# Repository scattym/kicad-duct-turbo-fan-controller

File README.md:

# kicad-duct-turbo-fan-controller
Wifi enabled fan controller projects for the duct turbo (ducturbo), terrabloom and ac infinity fans

Simple project marrying up 3 premade boards, the esp32 doit v2, a buck-boost board and a scd41 board.

Connects to the ducturbo 3.5mm to PWM control the fan speed.

Low side mosfet PWM chosen so that removal (or potentially failure) of the esp32 keeps the fan off.

Board will also work with the AC Infinity fans however there seems to be in internal 10k resistor on these fans, so changing R5 from 10K to 1K is needed to get the "off" voltage down to under 1 volt. With the following pins:

GND → GND

10V → VBUS

PWM → D+

TACH → D-

duct-turbo-fan-controller - original based of esp32 doit it board - done - tested

duct-turbo-fan-controller-v2 - moved to esp32-c3-wroom-02 - done - waiting testing

duct-turbo-fan-controller-v3 - add bme680 on board allow usb to power esp for programming - done - untested

duct-turbo-fan-controller-v4 - on board buck converter and on board scd41 - done - waiting testing

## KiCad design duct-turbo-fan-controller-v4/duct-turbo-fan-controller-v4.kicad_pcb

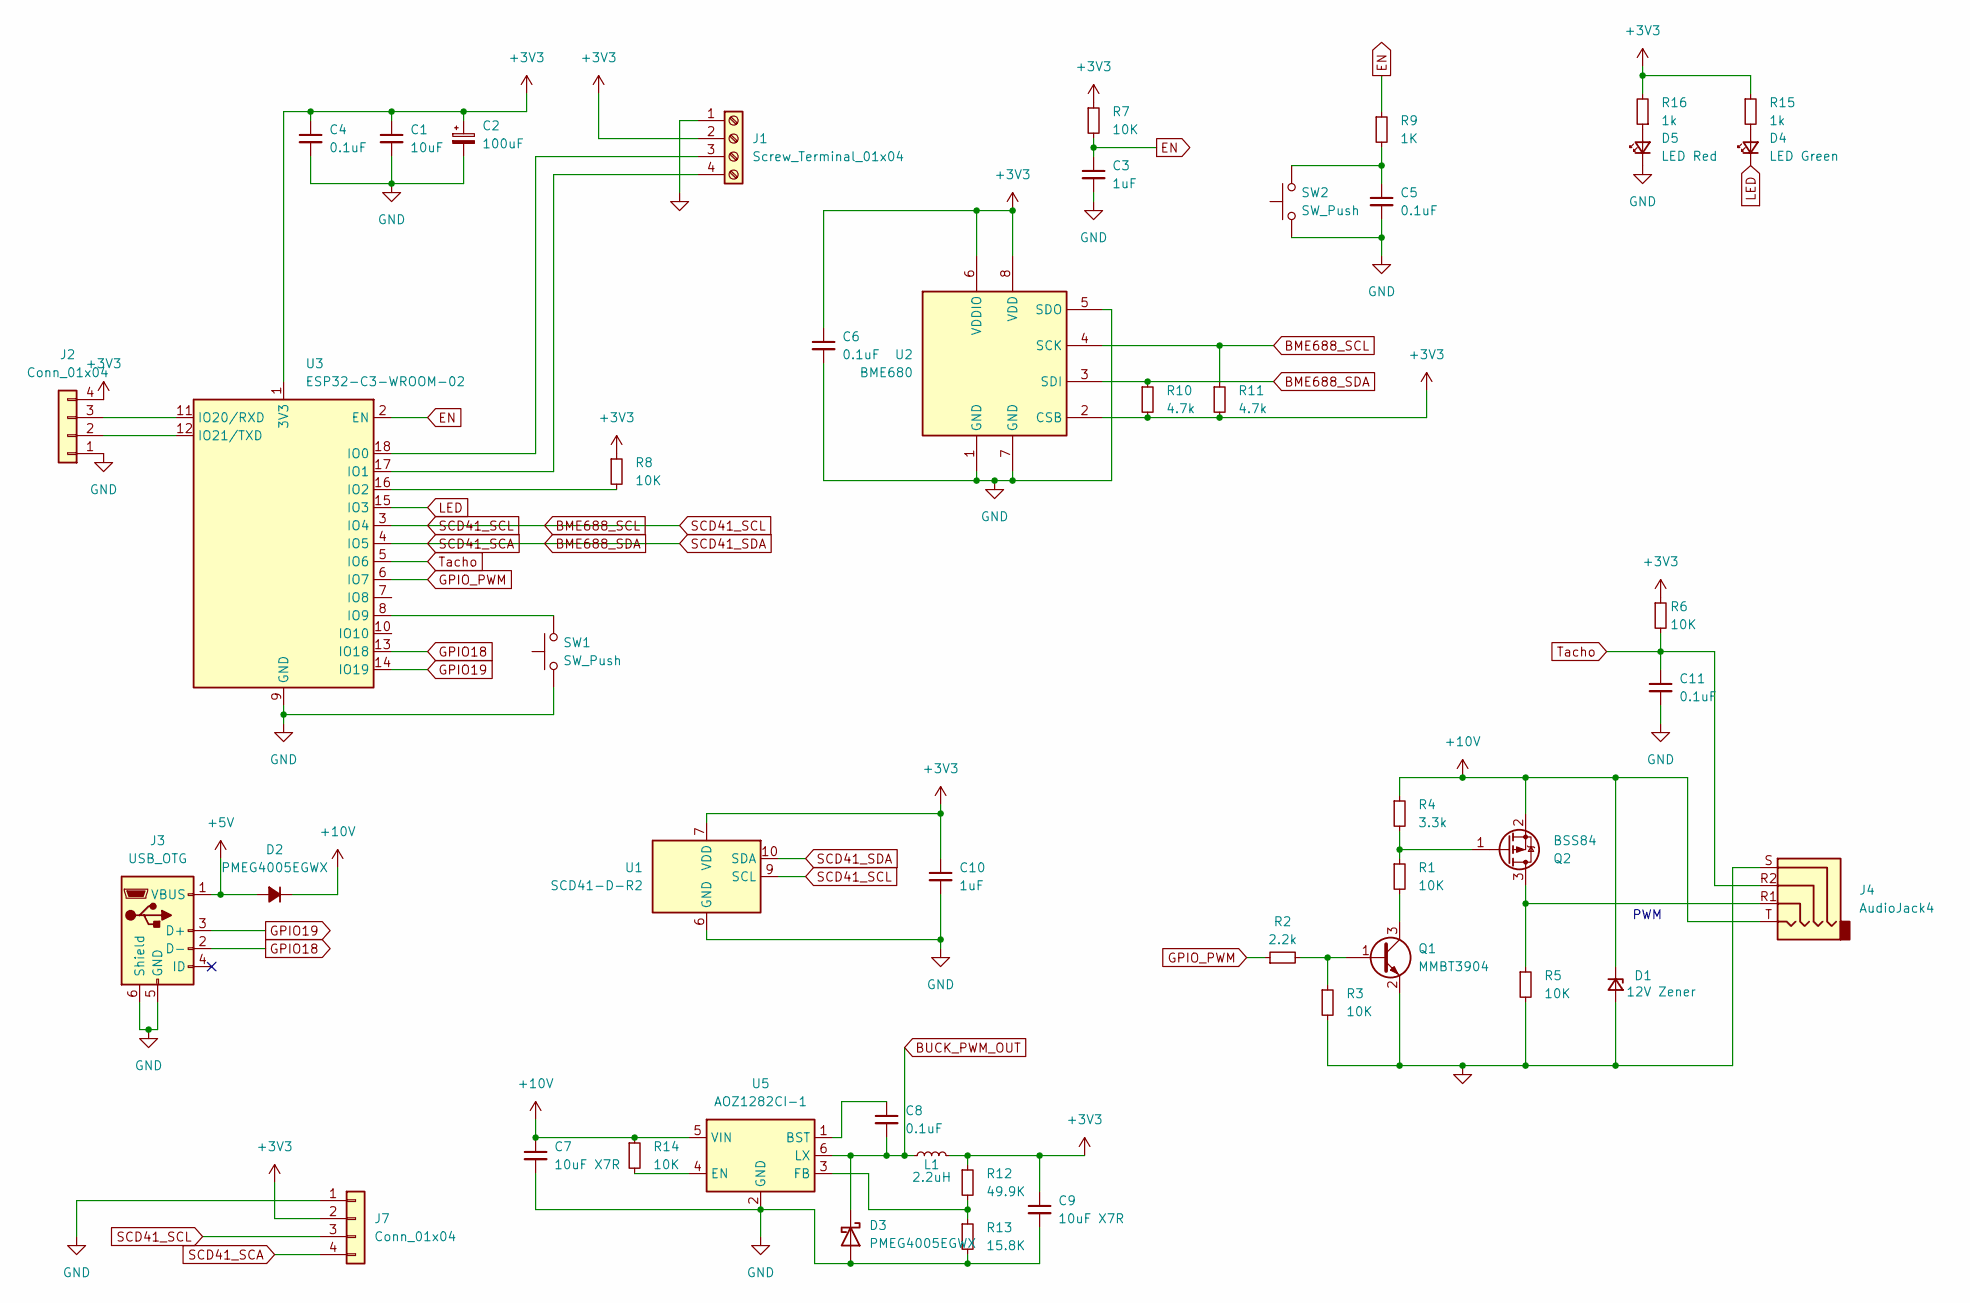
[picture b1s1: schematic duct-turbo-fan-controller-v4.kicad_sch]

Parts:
C1: 10uF; C_0805_2012Metric_Pad1.18x1.45mm_HandSolder
C2: 100uF; CP_EIA-3528-12_Kemet-T_Pad1.50x2.35mm_HandSolder
C3, C10: 1uF; C_0805_2012Metric_Pad1.18x1.45mm_HandSolder
C4, C5, C8: 0.1uF; C_0805_2012Metric_Pad1.18x1.45mm_HandSolder
C6, C11: 0.1uF; C_0603_1608Metric_Pad1.08x0.95mm_HandSolder
C7, C9: 10uF X7R; C_0805_2012Metric_Pad1.18x1.45mm_HandSolder
D1: 12V Zener; D_0805_2012Metric_Pad1.15x1.40mm_HandSolder
D2, D3: PMEG4005EGWX; D_SOD-123
D4: LED Green; LED_0603_1608Metric_Pad1.05x0.95mm_HandSolder
D5: LED Red; LED_0603_1608Metric_Pad1.05x0.95mm_HandSolder
J1: Screw_Terminal_01x04; TerminalBlock_Phoenix_MPT-0,5-4-2.54_1x04_P2.54mm_Horizontal
J2, J7: Conn_01x04; PinHeader_1x04_P2.54mm_Vertical
J3: USB_OTG; USB_Micro-B_Molex-105017-0001
J4: AudioJack4; Jack_3.5mm_KoreanHropartsElec_PJ-320D-4A_Horizontal
L1: 2.2uH; L_Bourns-SRN4018
Q1: MMBT3904; SOT-23
Q2: BSS84; SOT-23
R1, R3, R5, R7, R14: 10K; R_0805_2012Metric_Pad1.20x1.40mm_HandSolder
R2: 2.2k; R_0805_2012Metric_Pad1.20x1.40mm_HandSolder
R4: 3.3k; R_0805_2012Metric_Pad1.20x1.40mm_HandSolder
R6, R8: 10K; R_0603_1608Metric_Pad0.98x0.95mm_HandSolder
R9: 1K; R_0805_2012Metric_Pad1.20x1.40mm_HandSolder
R10, R11: 4.7k; R_0603_1608Metric_Pad0.98x0.95mm_HandSolder
R12: 49.9K; R_0805_2012Metric_Pad1.20x1.40mm_HandSolder
R13: 15.8K; R_0805_2012Metric_Pad1.20x1.40mm_HandSolder
R15, R16: 1k; R_0603_1608Metric_Pad0.98x0.95mm_HandSolder
SW1, SW2: SW_Push; SW_SPST_CK_RS282G05A3
U1: SCD41-D-R2; Sensirion_SCD4x-1EP_10.1x10.1mm_P1.25mm_EP4.8x4.8mm
U2: BME680; Bosch_LGA-8_3x3mm_P0.8mm_ClockwisePinNumbering
U3: ESP32-C3-WROOM-02
U5: AOZ1282CI-1; SOT-23-6

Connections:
+3V3: C1.1, C2.1, C4.1, C6.1, C9.1, C10.1, J1.2, J2.4, J7.2, L1.2, R6.1, R7.1, R8.1, R10.2, R11.2, R12.1, R15.1, R16.2, U1.7 (VDD), U1.19 (VDD), U2.2 (CSB), U2.6 (VDDIO), U2.8 (VDD), U3.1 (3V3)
+5V: D2.2 (A), J3.1 (VBUS)
+10V: C7.1, D1.1 (K), D2.1 (K), J4.T, Q2.2 (S), R4.1, R14.1, U5.5 (VIN)
BME688_SCL: J7.3, R11.1, U1.9 (SCL), U2.4 (SCK), U3.3 (IO4)
BME688_SDA: J7.4, R10.1, U1.10 (SDA), U2.3 (SDI), U3.4 (IO5)
BUCK_PWM_OUT: C8.2, D3.1 (K), L1.1, U5.6 (LX)
EN: C3.1, R7.2, R9.1, U3.2 (EN)
GND: C1.2, C2.2, C3.2, C4.2, C5.2, C6.2, C7.2, C9.2, C10.2, C11.2, D1.2 (A), D3.2 (A), D5.1 (K), J1.1, J2.1, J3.5 (GND), J3.6 (Shield), J4.S, J7.1, Q1.2 (E), R3.2, R5.2, R13.2, SW1.1, SW2.1, U1.6 (GND), U1.20 (GND), U1.21 (GND), U2.1 (GND), U2.5 (SDO), U2.7 (GND), U3.9 (GND), U3.19 (GND), U5.2 (GND)
GPIO18: J3.2 (D-), U3.13 (IO18)
GPIO19: J3.3 (D+), U3.14 (IO19)
GPIO_PWM: R2.1, U3.6 (IO7)
LED: D4.1 (K), U3.15 (IO3)
unnamed: C5.1, R9.2, SW2.2
unnamed: D4.2 (A), R15.2
unnamed: D5.2 (A), R16.1
unnamed: J1.3, U3.18 (IO0)
unnamed: J1.4, U3.17 (IO1)
unnamed: J2.2, U3.12 (IO21/TXD)
unnamed: J2.3, U3.11 (IO20/RXD)
unnamed: Q1.1 (B), R2.2, R3.1
unnamed: Q1.3 (C), R1.2
unnamed: J4.R1, Q2.3 (D), R5.1
unnamed: Q2.1 (G), R1.1, R4.2
unnamed: R8.2, U3.16 (IO2)
unnamed: SW1.2, U3.8 (IO9)
unnamed: C8.1, U5.1 (BST)
unnamed: R14.2, U5.4 (EN)
unnamed: R12.2, R13.1, U5.3 (FB)
Tacho: C11.1, J4.R2, R6.2, U3.5 (IO6)

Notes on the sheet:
PWM

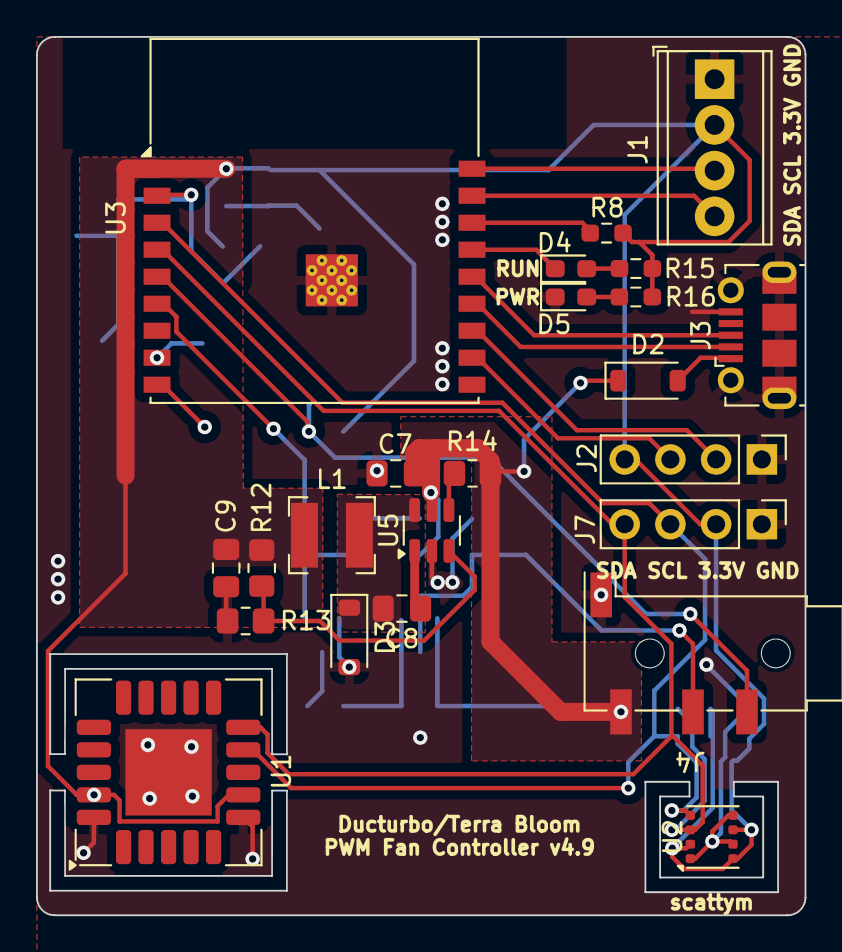
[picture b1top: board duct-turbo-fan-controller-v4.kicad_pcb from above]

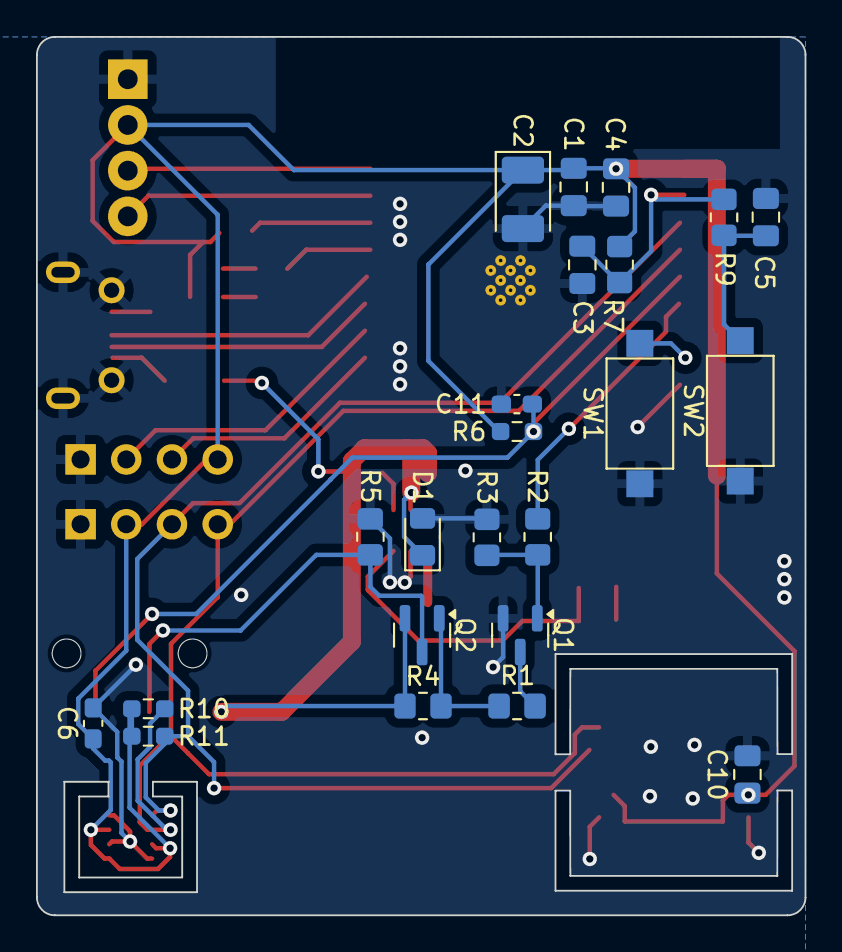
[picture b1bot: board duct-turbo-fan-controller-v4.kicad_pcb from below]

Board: 2 copper layers, 42.7 x 48.8 mm, 46 parts (23 on the bottom side), 29 nets.

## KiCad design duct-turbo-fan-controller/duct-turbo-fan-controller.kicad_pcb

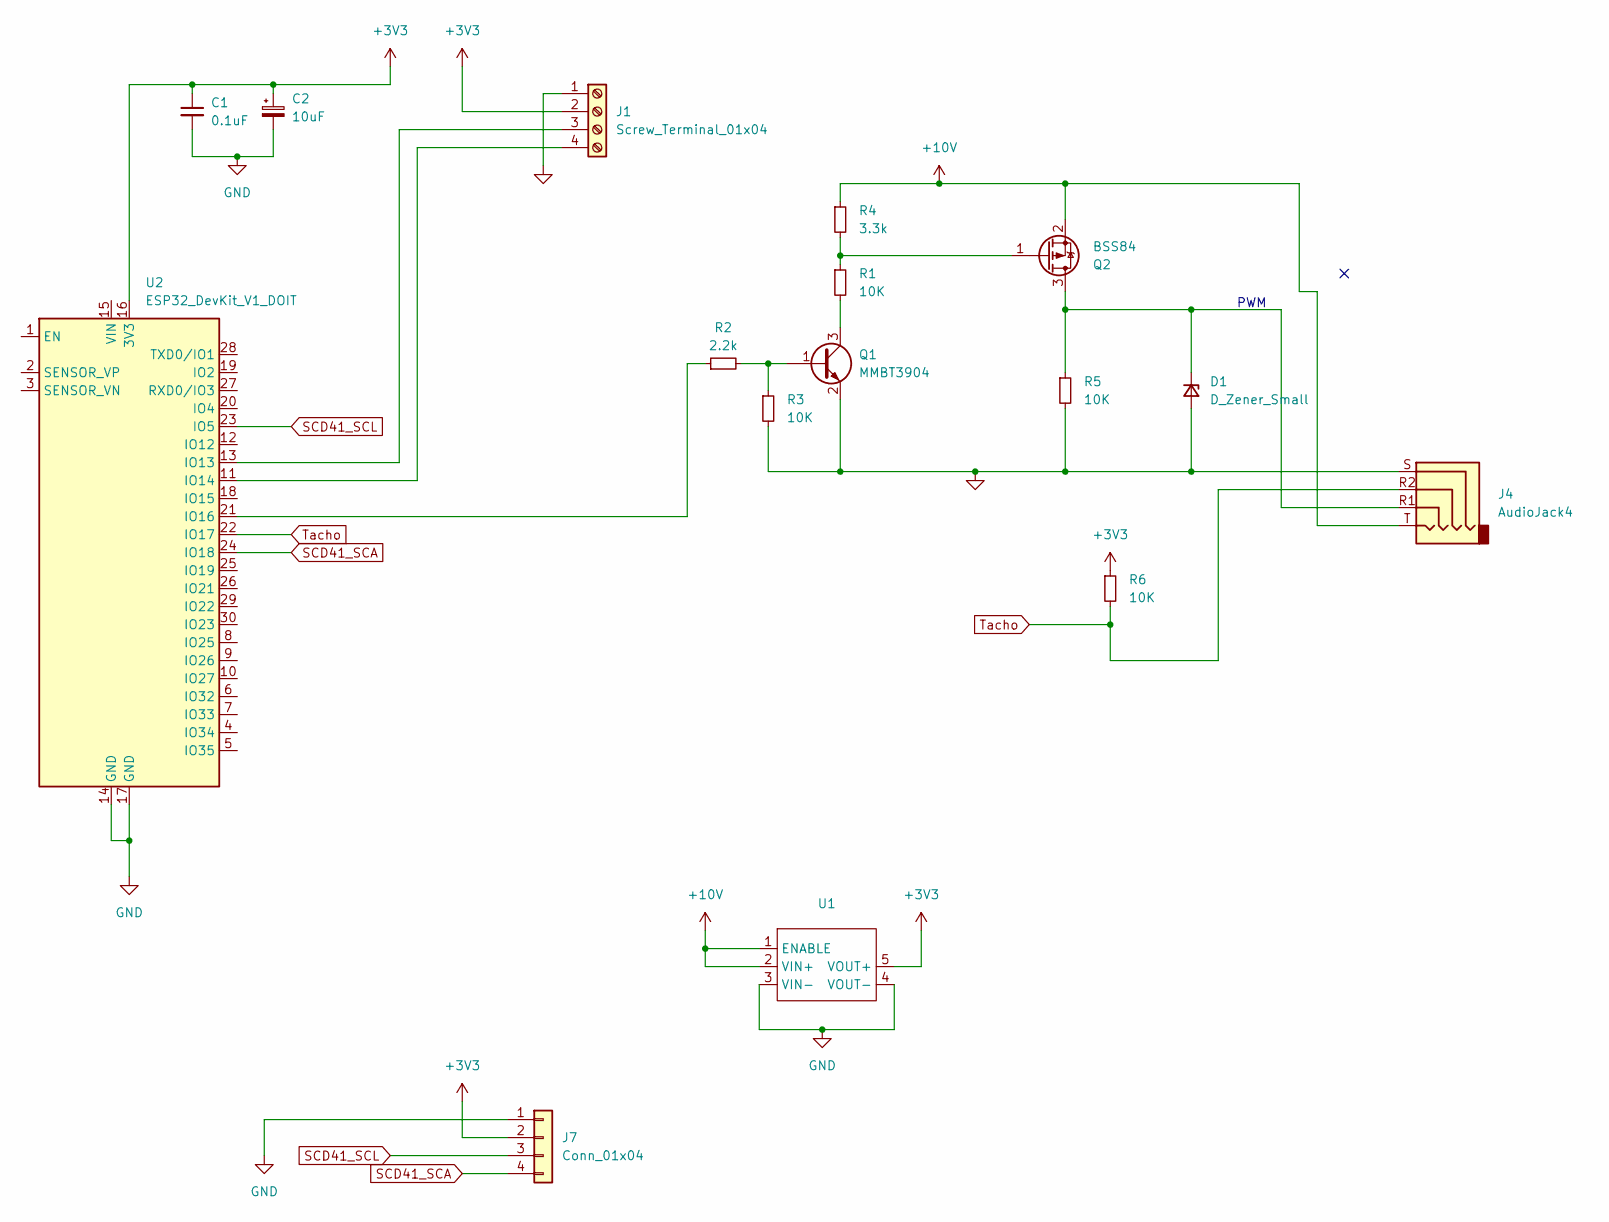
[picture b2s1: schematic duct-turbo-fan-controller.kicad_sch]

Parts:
C1: 0.1uF; C_0805_2012Metric_Pad1.18x1.45mm_HandSolder
C2: 10uF; CP_EIA-3528-12_Kemet-T_Pad1.50x2.35mm_HandSolder
D1: D_Zener_Small; D_0805_2012Metric_Pad1.15x1.40mm_HandSolder
J1: Screw_Terminal_01x04; TerminalBlock_Phoenix_MPT-0,5-4-2.54_1x04_P2.54mm_Horizontal
J4: AudioJack4; Jack_3.5mm_KoreanHropartsElec_PJ-320D-4A_Horizontal
J7: Conn_01x04; PinHeader_1x04_P2.54mm_Vertical
Q1: MMBT3904; SOT-23
Q2: BSS84; SOT-23
R1, R3, R5, R6: 10K; R_0805_2012Metric_Pad1.20x1.40mm_HandSolder
R2: 2.2k; R_0805_2012Metric_Pad1.20x1.40mm_HandSolder
R4: 3.3k; R_0805_2012Metric_Pad1.20x1.40mm_HandSolder
U1: Buck-Boost-Converter-Board-3.3V
U2: ESP32_DevKit_V1_DOIT; esp32_devkit_v1_doit

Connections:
+3V3: C1.1, C2.1, J1.2, J7.2, R6.1, U1.5 (VOUT+), U2.16 (3V3)
+10V: J4.T, Q2.2 (S), R4.1, U1.1 (ENABLE), U1.2 (VIN+)
GND: C1.2, C2.2, D1.2 (A), J1.1, J4.S, J7.1, Q1.2 (E), R3.2, R5.2, U1.3 (VIN-), U1.4 (VOUT-), U2.14 (GND), U2.17 (GND)
unnamed: D1.1 (K), J4.R1, Q2.3 (D), R5.1
unnamed: J1.3, U2.13 (IO13)
unnamed: J1.4, U2.11 (IO14)
unnamed: Q1.1 (B), R2.2, R3.1
unnamed: Q1.3 (C), R1.2
unnamed: Q2.1 (G), R1.1, R4.2
unnamed: R2.1, U2.21 (IO16)
SCD41_SCA: J7.4, U2.24 (IO18)
SCD41_SCL: J7.3, U2.23 (IO5)
Tacho: J4.R2, R6.2, U2.22 (IO17)

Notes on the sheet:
PWM

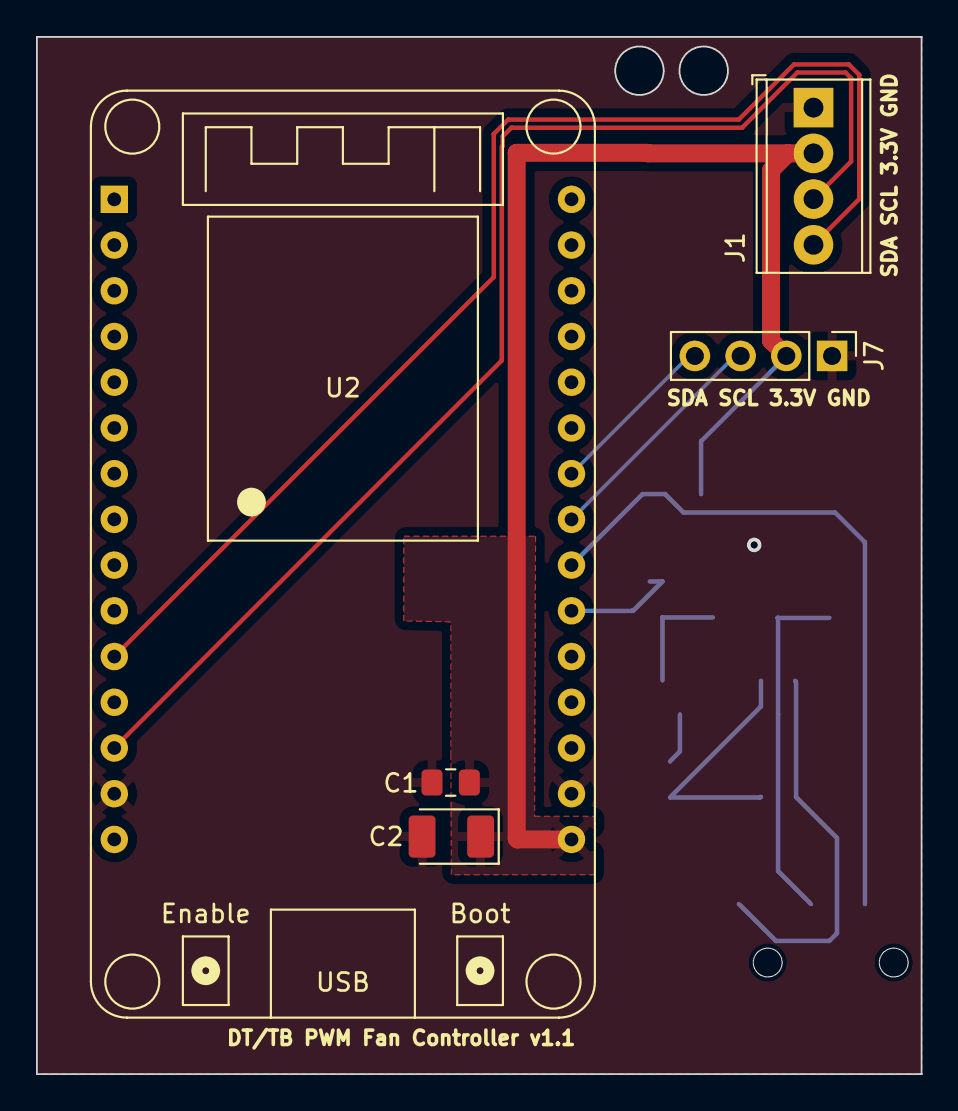
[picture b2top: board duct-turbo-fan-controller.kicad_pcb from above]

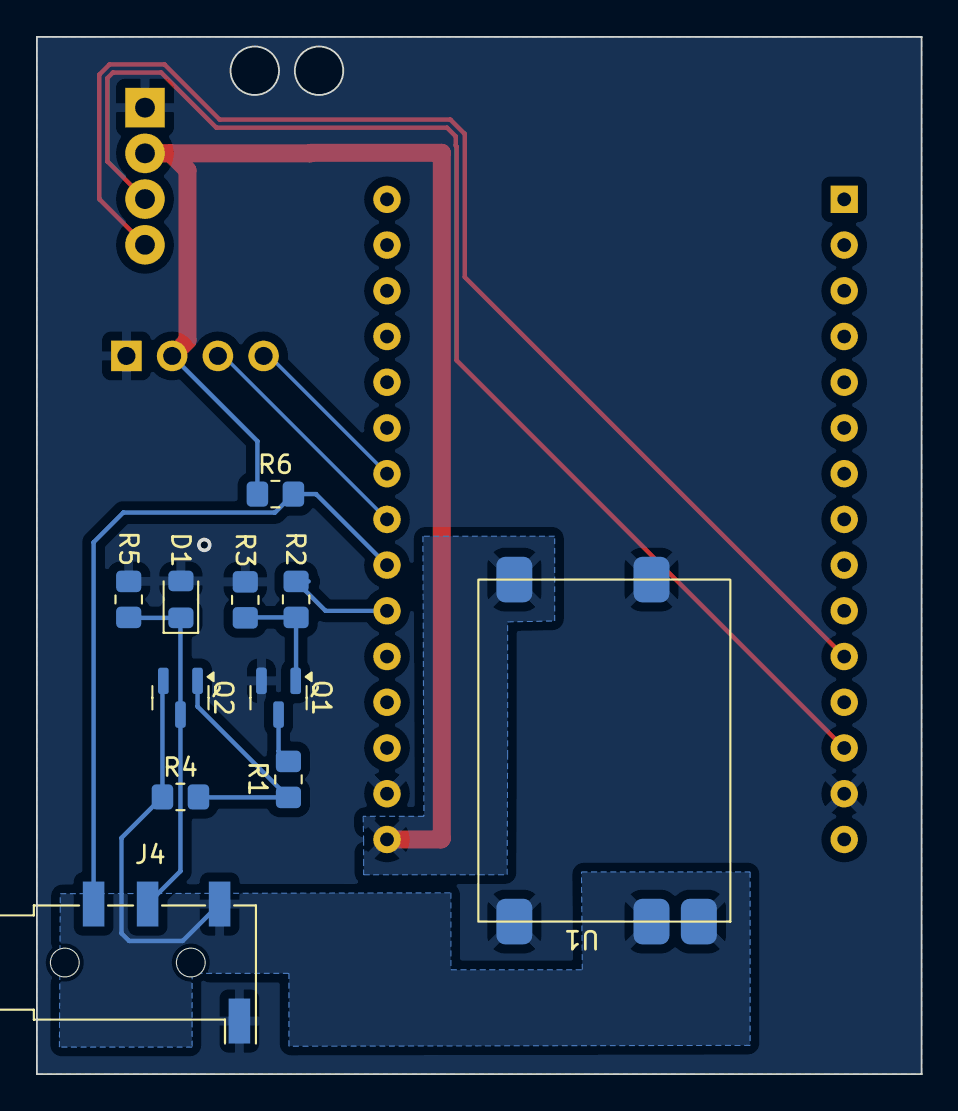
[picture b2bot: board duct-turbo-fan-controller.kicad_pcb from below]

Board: 2 copper layers, 49.1 x 57.6 mm, 16 parts (11 on the bottom side), 13 nets.

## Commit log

2025-01-06 Import of duct turbo fan controller
2025-01-06 Update to the readme.
2025-01-06 Update README.md
    Fix project name
2025-01-06 Update README.md
    Mappings on separate lines.
2025-01-06 Add new export file
2025-01-06 Remove old esp32 pwm references.
2025-01-06 Add v2 board with embedded esp32 c3 chip
2025-01-07 Move 3.5mm jack and reduce board size. Fix GND of USB_OTG.
2025-01-07 Move 3.3v line away from grounding thermal pad.
2025-01-07 Update version number.
2025-01-07 Add GND via on input from 3.5mm jack
2025-01-07 Add gnd via as esp32 thermal pad will not be soldered.
2025-01-07 Bump board version
2025-01-11 Update README.md
    Update to readme
2025-01-14 Start working on v3 with bme68X
2025-01-14 Google ownership verification.
2025-01-15 Remove google verfication file.
2025-01-15 Connecting up the bme680/688 in pcb layout
2025-01-15 Update track location to get more real estate for buck converter
2025-01-16 Fix missing ground on bme68x
2025-01-16 Add diode from usb 5v to power in.
2025-01-16 Bump version for next release
2025-01-16 New design with on-board buck converter
2025-01-17 Move to smaller inductor as buck switch is 1MHz
2025-01-17 Round the edges of the board
2025-01-17 Add label for pull up. Add tag.
2025-01-19 Add scd41 to the board.
2025-01-19 Shorter route for the 3.3v line to scd41
2025-01-19 New tag for the v4 board
2025-01-19 A couple of minor routing changes
2025-01-20 Add missing GND connection for SCD41
    Add example esphome home configurations for each board. Not complete.
2025-01-20 Increase size of 3.3v net to esp32
2025-01-20 New tag for v4 board
2025-01-20 Ignore .zip files from git
2025-01-22 Increase size of cutouts to 0.8mm as per pcbway spec.
2025-01-22 Move ground via to be fully enclosed
2025-01-22 Increase size of the track from 10V in to Buck converter
2025-01-23 Add capacitance close to sc41 for ripple reduction.
2025-01-23 Bump board version to 4.5
2025-01-23 Move capacitance closer to scd41
2025-01-23 Add missing schottky diode on the pwm output
2025-01-23 Extra GND vias to help dissipate buck converter thermals
2025-01-28 Updates to the labels on diodes and inductors
2025-01-31 Add LEDs to PCB to help identify state.
2025-02-02 Reduce size of R8 to 0603. Improve labels of LEDs.
2025-02-02 Update version number ready for tagging
2025-02-05 Add values to led resistors. Redraw zone fills.
2025-02-07 Fix a couple of schematic errors.
    1. External PWM was tied to ground.
    2. BME688 SCA and SCL pins were tied together.
2025-02-07 Bump board version.
2025-02-07 Fill redraw
2025-02-07 Add symbols for the smd usbc.
    May need to find different devices as reported that
    the pins are only vbus and gnd with no data pins.
2025-02-07 Add gnd tracks where fill zone incomplete.
    Update leds in schematic to be more readable.
2025-02-14 Updates to board
2025-02-14 Fix footprint for buck diode in schematic.
    Add values for buck capacitors in schematic.
2025-02-14 Fix buck diode footprint in pcb
2025-02-14 Fix buck diode footprint on pcb
2025-02-18 Add input resistor from Tacho pin
2025-03-08 Fix bme688 wiring by adding +3.3V to CSB pin.
    Was defaulting to spi mode and taking out the whole i2c link
2025-03-09 Fix labelling of the power and run leds.
    They were the wrong way around.
2025-05-26 Add filter capacitor to input tacho pin.
2025-05-26 Bump board version to v4.9
2025-05-29 Reduce size of scd41 cap to 0805
2025-11-09 Clean up to avoid overlapping wires.
